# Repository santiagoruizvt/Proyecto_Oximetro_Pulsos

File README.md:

# **Proyecto_Oximetro_Pulsos**
*Repositorio destinado para el proyecto de la materia Técnicas Digitales 3*

## Se encuentra disponible en la carpeta "Documentos" el preinforme del proyecto.
## Se encuentra disponible en la carpeta "Documentos" el informe final del proyecto.
## Se agrega el código desarrollado con STM32CubeIDE, con las siguientes configuraciones:

- UART: Se utilizará para la comunicación con el módulo bluetooth HM10.
	- PA2: TX
	- PA3: RX

- SPI: Se utilizará para la comunicación con el módulo R/W de tarjetas Micro SD
	- PB12: CSS
	- PB13: SCK
	- PB14: MISO
	- PB15: MOSI

- I2C1: Se utilizará para la comunicación con el módulo oxímetro MAX30100
	- PB6: SCL
	- PB7: SDA

- I2C2: Se utilizará para la comunicación con la pantalla OLED SSD1306
	- PB10: SCL
	- PB11: SDA

- PULSADOR: Se utilizará para comenzar con la medición.
	- PC14: PULL-UP

# Modelos 3D

## Diseños realizados con Fusion 360 (Autodesk)

# PROYECTO FINALIZADO

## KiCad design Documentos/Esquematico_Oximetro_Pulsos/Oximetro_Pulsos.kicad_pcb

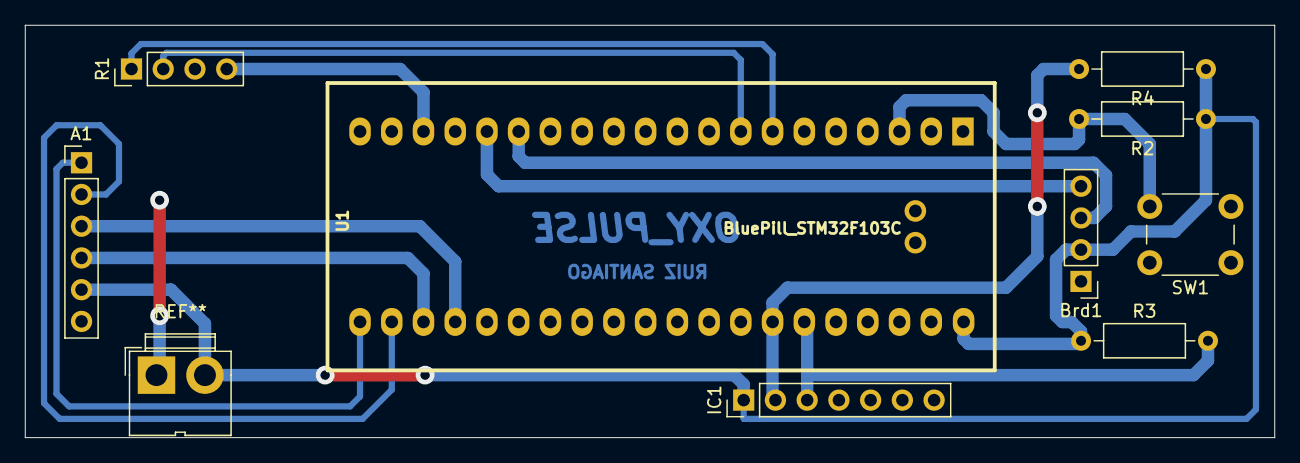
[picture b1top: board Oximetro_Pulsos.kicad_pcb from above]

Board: 2 copper layers, 100.0 x 33.0 mm, 9 parts (0 on the bottom side), 13 nets.

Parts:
A1: SD_Card_Module; PinHeader_1x06_P2.54mm_Vertical
Brd1: SSD1306; PinHeader_1x04_P2.54mm_Vertical
IC1: MAX30102; PinHeader_1x07_P2.54mm_Vertical
R1: hm10; PinHeader_1x04_P2.54mm_Vertical
R2: R; R_Axial_DIN0207_L6.3mm_D2.5mm_P10.16mm_Horizontal
R3, R4: 4K7; R_Axial_DIN0207_L6.3mm_D2.5mm_P10.16mm_Horizontal
SW1: SW_Push; SW_PUSH_6mm_H13mm
U1: BluePill_STM32F103C

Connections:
+3V3: A1.5, Brd1.2, IC1.1, R1.4, R2.1, R3.1, R4.1, U1.18, U1.40
GND: A1.6, Brd1.1, IC1.7, R1.3, SW1.1, U1.19, U1.20, U1.39
unnamed: A1.1, U1.21
unnamed: A1.3, U1.24
unnamed: A1.2, U1.22
unnamed: A1.4, U1.23
unnamed: Brd1.3, U1.15
unnamed: Brd1.4, U1.16
unnamed: IC1.2, R4.2, U1.34
unnamed: IC1.3, R3.2, U1.35
unnamed: R1.2, U1.8
unnamed: R1.1, U1.7
unnamed: R2.2, SW1.2, U1.3

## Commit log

2022-07-01 Agregado del archivo de ideas de proyecto
2022-07-14 Agregado del preinforme del proyecto
2022-07-14 Readme actualizado
2022-07-28 Primer commit del proyecto. Configuraciones del IOC para habilitar UART,I2C y SPI.
2022-07-28 Agregado de CSS y formato del README.
2022-07-28 Corrección de README
2022-07-28 Corrección del README
2022-07-28 Programacion LCD actualizada
2022-08-09 Agregado de la función del Bluetooth y algunas librerías para el MAX30100.
2022-09-26 Programación de funciones en MAX30100 No mide correctamente, pero se reciben valores del sensor y se realiza el procesamiento. En busca de errores.
2022-10-15 Correccion en lectura de FIFO Falta agregar promediado de valores de BPM y SPO2
2022-11-18 Integracion de modulos, no funciona la SD
2022-12-01 Código estable con mediciones correctas de BPM y SPO2
2022-12-01 Agregado de documentación, imagenes e informes.
2022-12-01 Agregado de imagenes en el README
2022-12-02 Informe final con índice actualizado
